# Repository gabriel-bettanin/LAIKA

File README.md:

# laika
Affordable robotic's actuator for dynamic robots

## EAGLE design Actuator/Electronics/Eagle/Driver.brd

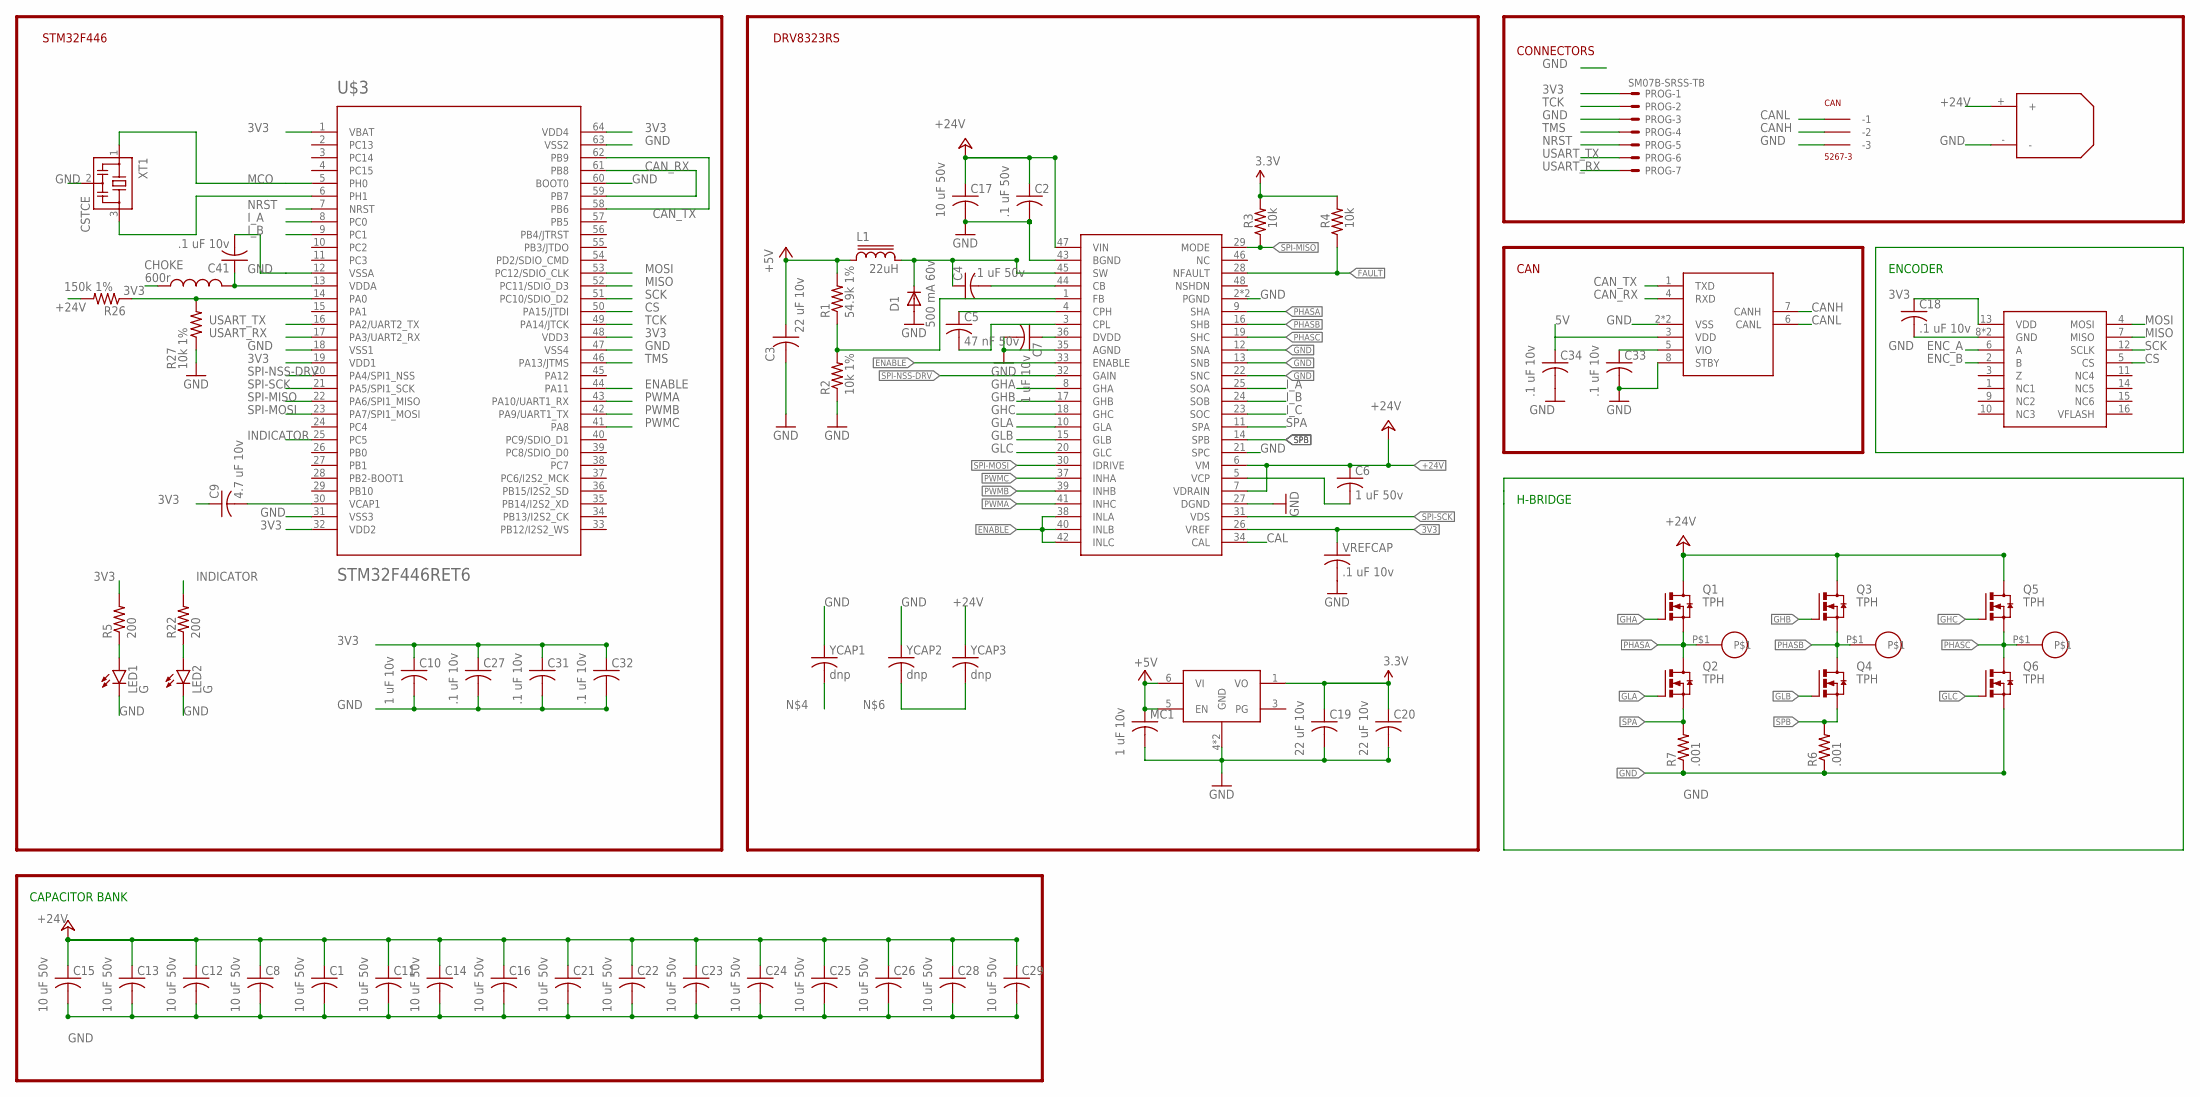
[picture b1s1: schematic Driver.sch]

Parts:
C1, C8, C11, C12, C13, C14, C15, C16, C17, C21, C22, C23, C24, C25, C26, C28, C29: 10 uF 50v; C1206K
C2, C4: .1 uF 50v; C0603K
C3, C19, C20: 22 uF 10v; C0603K
C5: 47 nF 50v; C0402K
C6: 1 uF 50v; C0603K
C7, C10: 1 uF 10v; C0402K
C9: 4.7 uF 10v; C0402K
C18, C27, C31, C32, C33, C34, C41: .1 uF 10v; C0402K
CAN: 5267-3
CHOKE: 600r; 0603
D1: 500 mA 60v; SOD123
L1: 22uH; SDR0302
LDFM33PUR: LDFM; DFN6-3X3
LED1, LED2: G; LED-0603
MC1: 1 uF 10v; C0402K
PROG: SM07B-SRSS-TB
Q1, Q2, Q3, Q4, Q5, Q6: TPH; TRANS_TPH5900CNH,L1Q
R1: 54.9k 1%; R0402
R2, R27: 10k 1%; R0402
R3, R4: 10k; R0402
R5, R22: 200; R0402
R6, R7: .001; R1210
R26: 150k 1%; R0402
U$1: DRV8323RH; QFN50P700X700X90-49N
U$2, U$4, U$5: 18_AWG_PAD
U$3: STM32F446RET6; TQFP64
U$6: MCP2542; TDFN
U$9: XT30; XT30_HORIZONTAL
U$11: MA700; QFN16
VREFCAP: .1 uF 10v; C0402K
XT1: CSTCE
YCAP1, YCAP2, YCAP3: dnp; C0402K

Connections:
3V3: C9.1, C10.1, C18.1, C19.1, C20.1, C27.1, C31.1, C32.1, C33.1, CHOKE.1, LDFM33PUR.1 (VO), PROG.1, R3.2, R4.2, R5.2, U$1.26 (VREF), U$3.1 (VBAT), U$3.19 (VDD1), U$3.32 (VDD2), U$3.48 (VDD3), U$3.64 (VDD4), U$6.5 (VIO), U$11.13 (VDD), VREFCAP.1
5V: C3.1, C34.1, L1.1, LDFM33PUR.5 (EN), LDFM33PUR.6 (VI), MC1.1, R1.2, U$6.3 (VDD)
+24V: C1.1, C2.1, C6.1, C8.1, C11.1, C12.1, C13.1, C14.1, C15.1, C16.1, C17.1, C21.1, C22.1, C23.1, C24.1, C25.1, C26.1, C28.1, C29.1, Q1.5 (D), Q1.6 (D), Q1.7 (D), Q1.8 (D), Q1.EP (D), Q3.5 (D), Q3.6 (D), Q3.7 (D), Q3.8 (D), Q3.EP (D), Q5.5 (D), Q5.6 (D), Q5.7 (D), Q5.8 (D), Q5.EP (D), R26.2, U$1.6 (VM), U$1.7 (VDRAIN), U$1.47 (VIN), U$9.+, YCAP3.1
BOOT: C4.2, U$1.44 (CB)
CAL: U$1.34 (CAL)
CANH: CAN.P$2 (-2), U$6.7 (CANH)
CANL: CAN.P$1 (-1), U$6.6 (CANL)
CAN_RX: U$3.59 (PB7), U$3.61 (PB8), U$6.4 (RXD)
CAN_TX: U$3.58 (PB6), U$3.62 (PB9), U$6.1 (TXD)
CPH: C5.1, U$1.4 (CPH)
CPL: C5.2, U$1.3 (CPL)
CS: U$3.50 (PA15/JTDI), U$11.5 (CS)
DEVICE3.3: C7.1, U$1.36 (DVDD)
ENABLE: U$1.33 (ENABLE), U$1.38 (INLA), U$1.40 (INLB), U$1.42 (INLC), U$3.44 (PA11)
ENC_A: U$11.6 (A)
ENC_B: U$11.2 (B)
FAULT: R4.1, U$1.28 (NFAULT)
FB: R1.1, R2.2, U$1.1 (FB)
GHA: Q1.4 (G), U$1.8 (GHA)
GHB: Q3.4 (G), U$1.17 (GHB)
GHC: Q5.4 (G), U$1.18 (GHC)
GLA: Q2.4 (G), U$1.10 (GLA)
GLB: Q4.4 (G), U$1.15 (GLB)
GLC: Q6.4 (G), U$1.20 (GLC)
GND: C1.2, C2.2, C3.2, C7.2, C8.2, C10.2, C11.2, C12.2, C13.2, C14.2, C15.2, C16.2, C17.2, C18.2, C19.2, C20.2, C21.2, C22.2, C23.2, C24.2, C25.2, C26.2, C27.2, C28.2, C29.2, C31.2, C32.2, C33.2, C34.2, C41.2, CAN.P$3 (-3), D1.A, LDFM33PUR.4 (GND), LDFM33PUR.EXP (GND), LED1.C, LED2.C, MC1.2, PROG.3, Q6.1 (S), Q6.2 (S), Q6.3 (S), R2.1, R6.1, R7.1, R27.1, U$1.2 (PGND), U$1.12 (SNA), U$1.13 (SNB), U$1.21 (SPC), U$1.22 (SNC), U$1.27 (DGND), U$1.35 (AGND), U$1.43 (BGND), U$1.49 (PGND), U$3.12 (VSSA), U$3.18 (VSS1), U$3.31 (VSS3), U$3.47 (VSS4), U$3.60 (BOOT0), U$3.63 (VSS2), U$6.2 (VSS), U$6.8 (STBY), U$6.9 (VSS), U$9.-, U$11.8 (GND), U$11.TH (GND), VREFCAP.2, XT1.2, YCAP1.1, YCAP2.1
INDICATOR: R22.2, U$3.25 (PC5)
I_A: U$1.25 (SOA), U$3.8 (PC0)
I_B: U$1.24 (SOB), U$3.9 (PC1)
I_C: U$1.23 (SOC)
MCO: U$3.5 (PH0), XT1.1
MISO: U$3.52 (PC11/SDIO_D3), U$11.7 (MISO)
MOSI: U$3.53 (PC12/SDIO_CLK), U$11.4 (MOSI)
unnamed: LED1.A, R5.1
unnamed: C41.1, CHOKE.2, U$3.13 (VDDA)
unnamed: C9.2, U$3.30 (VCAP1)
unnamed: YCAP2.2, YCAP3.2
unnamed: R26.1, R27.2, U$3.14 (PA0)
unnamed: LED2.A, R22.1
unnamed: U$3.6 (PH1), XT1.3
NRST: PROG.5, U$3.7 (NRST)
PHASA: Q1.1 (S), Q1.2 (S), Q1.3 (S), Q2.5 (D), Q2.6 (D), Q2.7 (D), Q2.8 (D), Q2.EP (D), U$1.9 (SHA), U$4.P$1
PHASB: Q3.1 (S), Q3.2 (S), Q3.3 (S), Q4.5 (D), Q4.6 (D), Q4.7 (D), Q4.8 (D), Q4.EP (D), U$1.16 (SHB), U$2.P$1
PHASC: Q5.1 (S), Q5.2 (S), Q5.3 (S), Q6.5 (D), Q6.6 (D), Q6.7 (D), Q6.8 (D), Q6.EP (D), U$1.19 (SHC), U$5.P$1
PWMA: U$1.41 (INHC), U$3.43 (PA10/UART1_RX)
PWMB: U$1.39 (INHB), U$3.42 (PA9/UART1_TX)
PWMC: U$1.37 (INHA), U$3.41 (PA8)
SCK: U$3.51 (PC10/SDIO_D2), U$11.12 (SCLK)
SPA: Q2.1 (S), Q2.2 (S), Q2.3 (S), R7.2, U$1.11 (SPA)
SPB: Q4.1 (S), Q4.2 (S), Q4.3 (S), R6.2, U$1.14 (SPB)
SPI-MISO: R3.1, U$1.29 (MODE), U$3.22 (PA6/SPI1_MISO)
SPI-MOSI: U$1.30 (IDRIVE), U$3.23 (PA7/SPI1_MOSI)
SPI-NSS-DRV: U$1.32 (GAIN), U$3.20 (PA4/SPI1_NSS)
SPI-SCK: U$1.31 (VDS), U$3.21 (PA5/SPI1_SCK)
SW: C4.1, D1.C, L1.2, U$1.45 (SW)
TCK: PROG.2, U$3.49 (PA14/JTCK)
TMS: PROG.4, U$3.46 (PA13/JTMS)
USART_RX: PROG.7, U$3.17 (PA3/UART2_RX)
USART_TX: PROG.6, U$3.16 (PA2/UART2_TX)
VCP: C6.2, U$1.5 (VCP)

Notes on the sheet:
DRV8323RS
STM32F446
CAN
CONNECTORS
ENCODER
H-BRIDGE
CAPACITOR BANK

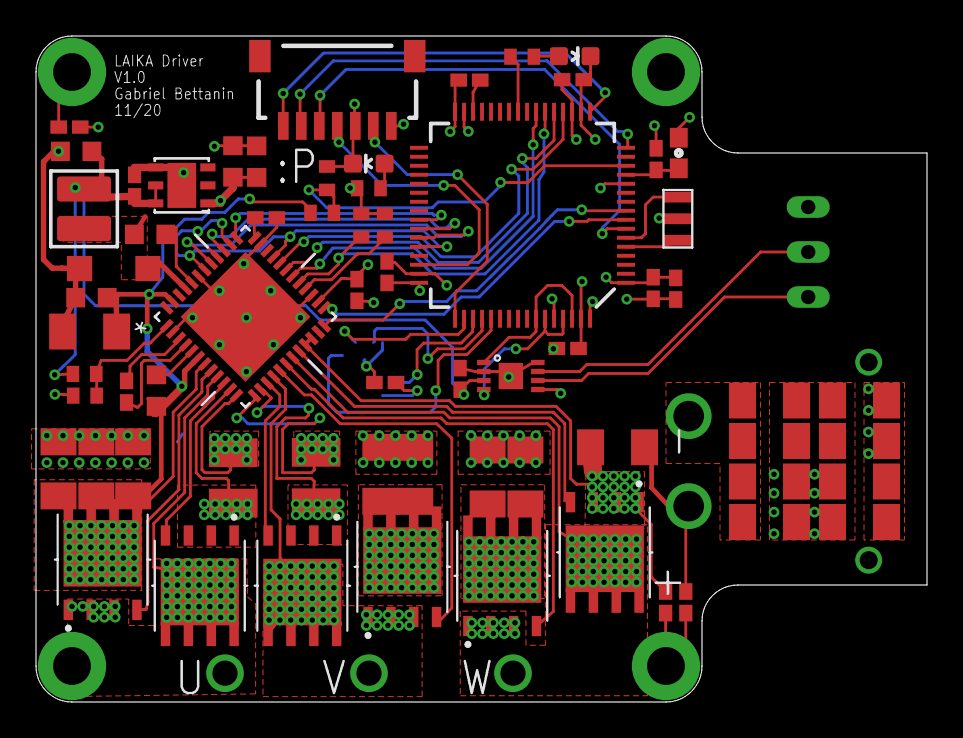
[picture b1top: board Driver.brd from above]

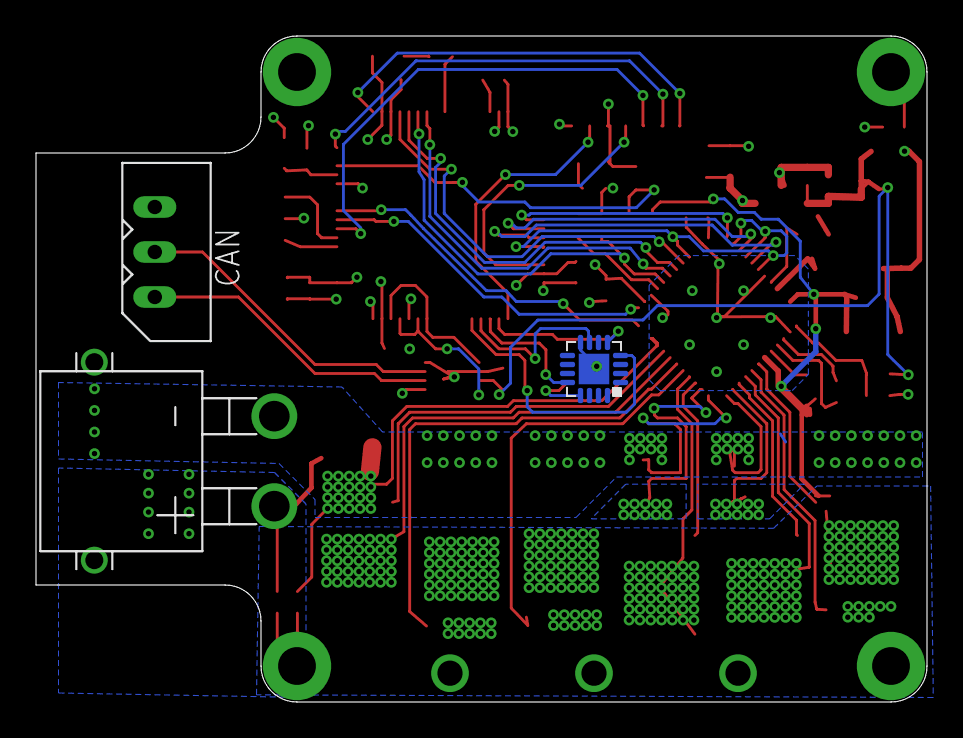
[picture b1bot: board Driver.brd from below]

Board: 4 copper layers, 49.5 x 37.0 mm, 72 parts (3 on the bottom side), 55 nets.

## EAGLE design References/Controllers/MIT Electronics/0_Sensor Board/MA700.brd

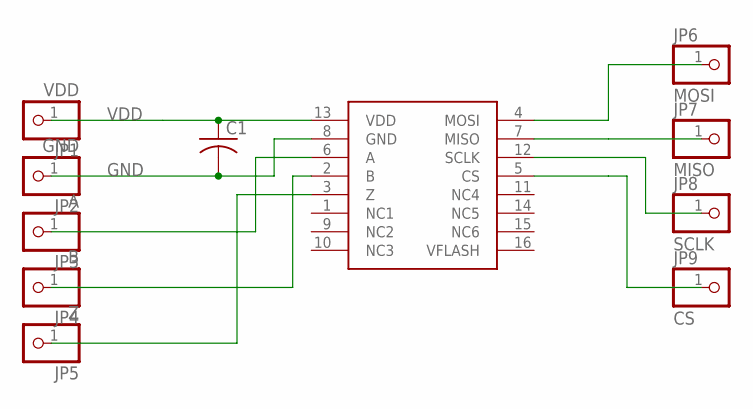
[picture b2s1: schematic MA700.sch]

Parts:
C1: C-USC0603; C0603
JP1: VDD; 1X01
JP2: GND; 1X01
JP3: A; 1X01
JP4: B; 1X01
JP5: Z; 1X01
JP6: MOSI; 1X01
JP7: MISO; 1X01
JP8: SCLK; 1X01
JP9: CS; 1X01
U$1: MA700; QFN16

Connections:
GND: C1.2, JP2.1, U$1.8 (GND)
unnamed: JP4.1, U$1.2 (B)
unnamed: JP9.1, U$1.5 (CS)
unnamed: JP3.1, U$1.6 (A)
unnamed: JP5.1, U$1.3 (Z)
unnamed: JP7.1, U$1.7 (MISO)
unnamed: JP8.1, U$1.12 (SCLK)
unnamed: JP6.1, U$1.4 (MOSI)
VDD: C1.1, JP1.1, U$1.13 (VDD)

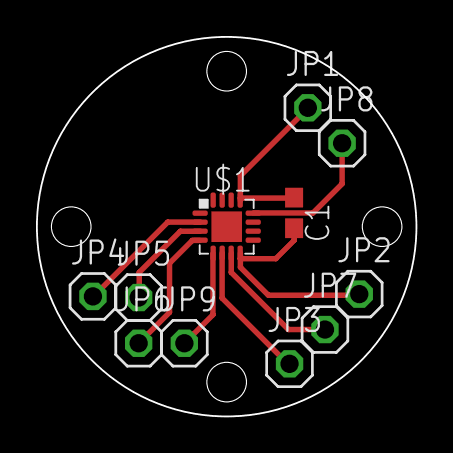
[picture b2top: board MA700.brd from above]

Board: 2 copper layers, 21.1 x 21.1 mm, 11 parts (0 on the bottom side), 9 nets.

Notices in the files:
parts and their libraries:
SparkFun-LED: Licensing: Creative Commons ShareAlike 4.0 International - https://creativecommons.org/licenses/by-sa/4.0
inductor-bourns: Copyright (C) 2008, Bob Starr
